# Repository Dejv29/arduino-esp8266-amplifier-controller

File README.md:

## **arduino-esp8266-amplifier-controller**  

Hybrid analog/digital amplifier controller with IR learning, motorized ALPS potentiometer feedback and ESP8266 web API.

# **Arduino + ESP8266 Amplifier Controller**  

This project is a comprehensive control system for a classic analog amplifier built using an Arduino Nano and ESP8266. The goal was to preserve the original analog character of the amplifier (including manual volume control) while adding modern features such as IR control, a web interface, a remote terrace panel, and a network API.  

The module is designed as an upgrade for a previous system based on the CD4017N microcontroller. The PCB is connected to a socket in place of the CD4017N.

### **Architecture**

The system is divided into two parts:  

#### **Arduino Nano**  

- Control of the ALPS motorized potentiometer (volume)  

- Reading the current position of the rotary volume knob via an analog input (with an added trim potentiometer for feedback)  

- IR receiver with the ability to learn up to 10 codes for each function (stored in EEPROM)  

- Control of input relays and speaker switching relays  

- RGB LED indication of the currently selected input  

#### **ESP8266**

- Web server with configuration and control interface  

- HTTP API for external control  

- Serial communication with the Arduino  

Both parts operate independently – a WiFi outage does not affect the basic functionality of the amplifier.  

### **Features**

#### **IR Learning (EEPROM)**  

Each function can have up to 10 different IR codes assigned:  

- Volume +  
- Volume -  
- Power  
- Input  
- Speakers  
- Media Play/Pause  
- Media Next  
- Media Previous  

This allows multiple remote controls to be used simultaneously.  

#### **Volume – Hybrid Solution**  

An ALPS motorized potentiometer is used.  

Analog position sensing has been added, which means:  

- the volume can be adjusted by the motor (IR, web, HW buttons)  
- it can also be changed manually by turning the knob  
- the Arduino always knows the current physical position  

This preserves full analog functionality while adding digital control.  

#### **Audio Inputs**  

- 6 inputs  
- RGB LED indicates the active input  
- Input 3 contains an internal Bluetooth module  
- Input 4 contains an external Bluetooth module located in the terrace panel  

Each input can have an individual maximum volume limit set to prevent speaker overload when different signal levels are used.  

#### **Speaker Switching**  

The **Speakers** function switches between:  

- Living room speakers  
- Terrace speakers  

#### **Terrace Control Panel**  

The external panel includes:  

- Hardware buttons for all functions  
- A rotary volume control  
- An IR receiver  

The amplifier can therefore be fully controlled even outside the main room.  

#### **Web Interface (ESP8266)**  

The ESP8266 runs a simple web server that allows:  

- Control of all amplifier functions  
- Learning and deleting IR codes  
- Setting maximum volume limits for individual inputs  
- Displaying the current device status  

#### **HTTP API**  

The server accepts commands in the following format:  

SET_POWER_ON / SET_POWER_OFF  

SET_VOLUME_25  

SET_INPUT_2  

SET_SPEAKER_A / SET_SPEAKER_B  

PULSE_VOLUP  

PULSE_VOLDOWN  

SET_AUTO_OFF_<value_in_seconds> / SET_AUTO_OFF_0 – cancels the timer  

IR_LEARN_POWER (VOLUP, VOLDOWN, INPUT, SPEAKERS, PLAY, NEXT, PREV)  

IR_REMOVE_POWER (VOLUP, VOLDOWN, INPUT, SPEAKERS, PLAY, NEXT, PREV )  

IR_REMOVE_POWER_ALL  

SET_MAX_VOL_INPUT__<volume_value>   (sets the specified volume value as the limit)

SET_CURRENT_MAX_VOLUME  (sets the current volume as the limit)

WIPE_EEPROM (clears the EEPROM memory)

Each request returns a response containing the complete current device status.  

This API can be easily integrated into other systems – for example into the **Tasker** app, where a simple control application using HTTP commands has been created.  

____________________________________________________________________________________________________________________________________________________________________________________________________________________________________________________________________________________________________________________________________________

# **Arduino + ESP8266 Amplifier Controller**  

Tento projekt je komplexní řídicí systém pro klasický analogový zesilovač postavený na Arduino Nano a  ESP8266. Cílem bylo zachovat původní analogový charakter zesilovače (včetně manuálního ovládání hlasitosti), ale doplnit jej o moderní funkce – IR ovládání, webové rozhraní, vzdálený panel na terase a síťové API. 

Modul je koncipován jako upgrade pro předchozí systém postavený na mikrokontroléru CD4017N. PCB je připojena do patice na místo CD4017N.

### **Architektura**

Systém je rozdělen na dvě části:  

#### **Arduino Nano**  

- Řízení motorizovaného potenciometru ALPS (hlasitost)  

- Snímání aktuální polohy otočného ovladače hlasitosti přes analogový vstup (přidaný trimr pro zpětnou vazbu)  

- IR přijímač s možností učení až 10 kódů na každou funkci (uloženo v EEPROM)  

- Ovládání relé vstupů a reproduktorových větví  

- RGB LED indikace aktuálního vstupu  

#### **ESP8266**

- Web server s konfiguračním a ovládacím rozhraním  

- HTTP API pro externí řízení  

- Sériová komunikace s Arduinem 

 Obě části fungují nezávisle – výpadek WiFi neovlivní základní funkčnost zesilovače.  

### **Funkce**

#### **IR učení (EEPROM)**  

Každé funkci lze přiřadit až 10 různých IR kódů:  

- Volume +  
- Volume -  
- Power  
- Input  
- Speakers  
- Media Play/Pause  
- Media Next  
- Media Previous  

To umožňuje používat více dálkových ovladačů současně.  

#### **Hlasitost – hybridní řešení**  

Použit je motorizovaný potenciometr ALPS.  

   Bylo doplněno analogové snímání polohy, takže:  
- hlasitost lze měnit motorem (IR, web, HW tlačítka)  
- lze ji měnit i ručně otočením knobu  
- Arduino vždy zná aktuální fyzickou polohu

 Zachována je tedy plná analogová funkčnost, ale s digitální kontrolou.  

#### **Audio vstupy**  

- 6 vstupů  
- RGB LED indikuje aktivní vstup  
- Na vstupu 3 je interní Bluetooth modul  
- Na vstupu 4 je externí Bluetooth modul umístěný v terasovém panelu  

 Pro každý vstup lze nastavit individuální maximální limit hlasitosti, aby nedošlo k přetížení reproduktorů při různých úrovních signálu.  

#### **Přepínání reproduktorů**  

Funkce **Speakers** přepíná mezi:  

- Reproduktory v obýváku  
- Reproduktory na terase  

#### **Terasový ovládací panel**  

Externí panel obsahuje:  

- HW tlačítka pro všechny funkce  
- Otočný ovladač hlasitosti  
- IR přijímač  

 Zesilovač je tedy plně ovladatelný i mimo hlavní místnost.  

#### **Webové rozhraní (ESP8266)**  

ESP8266 provozuje jednoduchý web server, který umožňuje:  

- Ovládání všech funkcí zesilovače  
- Učení a mazání IR kódů  
- Nastavení maximální hlasitosti pro jednotlivé vstupy  
- Zobrazení aktuálního stavu zařízení  

#### **HTTP API**  

Server přijímá příkazy ve formátu:  

SET_POWER_ON / SET_POWER_OFF  

SET_VOLUME_25  

SET_INPUT_2  

SET_SPEAKER_A / SET_SPEAKER_B

PULSE_VOLUP  

PULSE_VOLDOWN  

SET_AUTO_OFF_<hodnota_v_sekundách> / SET_AUTO_OFF_0 – zruší časovač 

IR_LEARN_POWER (VOLUP, VOLDOWN, INPUT, SPEAKERS, PLAY, NEXT, PREV)  

IR_REMOVE_POWER (VOLUP, VOLDOWN, INPUT, SPEAKERS, PLAY, NEXT, PREV )  

IR_REMOVE_POWER_ALL  

SET_MAX_VOL_INPUT__<hodnota_volume>   (nastaví zadanou hodnotu hlasitosti jako limit)

SET_CURRENT_MAX_VOLUME  (nastaví současnou hlasitost jako limit)

WIPE_EEPROM (vymaže paměť EEPROM)

​    

 Každý požadavek vrací odpověď obsahující kompletní aktuální stav zařízení.  

 Toto API lze snadno integrovat do jiných systémů – například do aplikace **Tasker**, kde je vytvořena jednoduchá ovládací aplikace využívající HTTP příkazy  

​

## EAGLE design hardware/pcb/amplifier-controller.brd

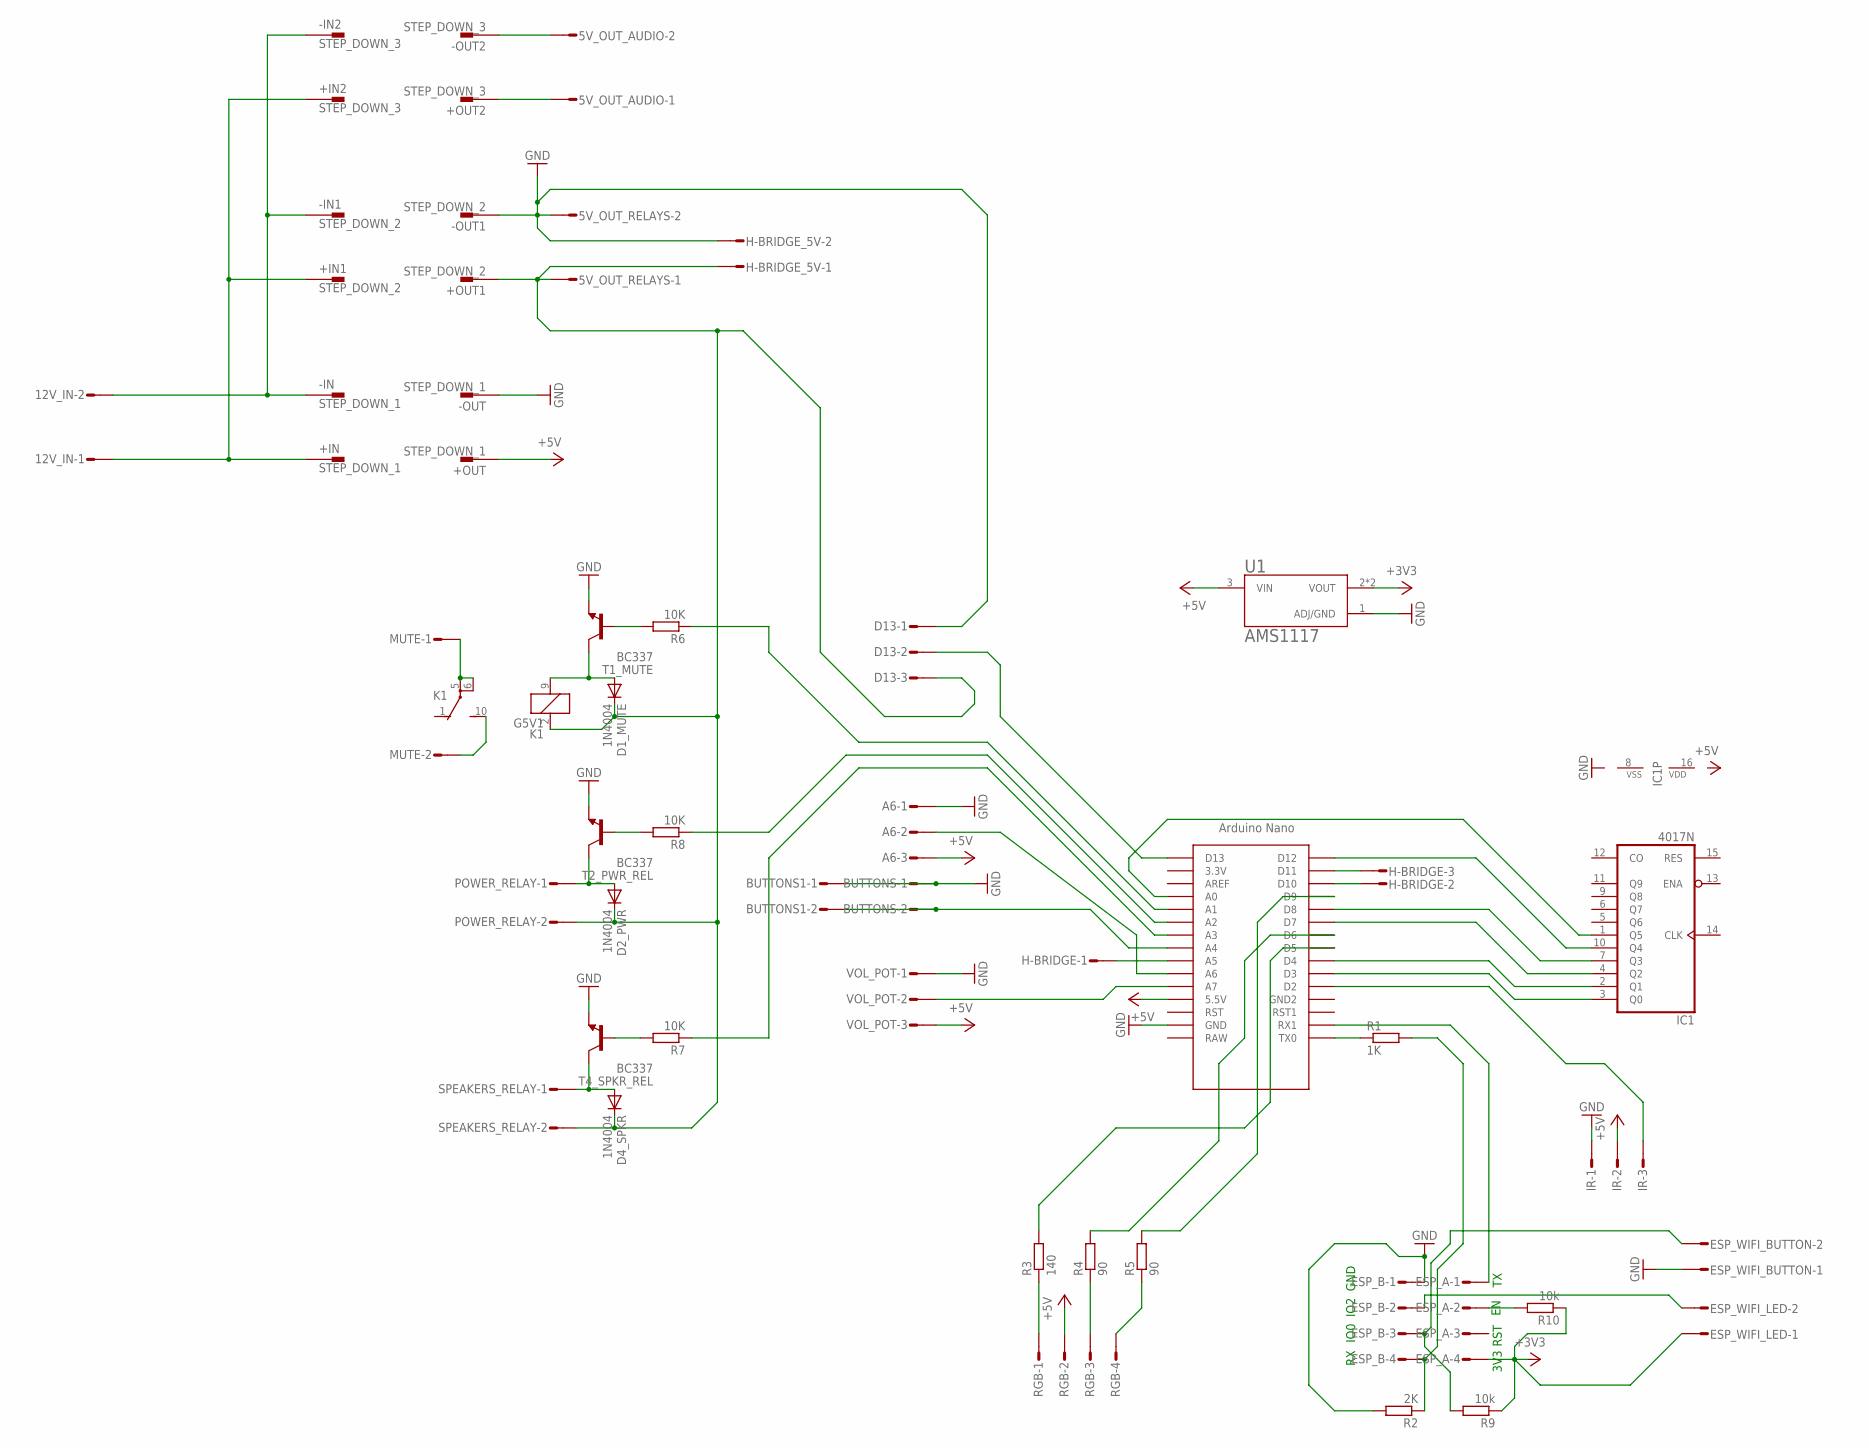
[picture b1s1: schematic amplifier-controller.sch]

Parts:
5V_OUT_AUDIO, 5V_OUT_RELAYS, 12V_IN: L02P
+IN: STEP_DOWN_1; 62221
+IN1: STEP_DOWN_2; 62221
+IN2: STEP_DOWN_3; 62221
+OUT: STEP_DOWN_1; 62221
+OUT1: STEP_DOWN_2; 62221
+OUT2: STEP_DOWN_3; 62221
-IN: STEP_DOWN_1; 62221
-IN1: STEP_DOWN_2; 62221
-IN2: STEP_DOWN_3; 62221
-OUT: STEP_DOWN_1; 62221
-OUT1: STEP_DOWN_2; 62221
-OUT2: STEP_DOWN_3; 62221
A6: L03P
BUTTONS, BUTTONS1: L02P
D1_MUTE, D2_PWR, D4_SPKR: 1N4004; DO41-10
D13: L03P
ESP_A: L04P
ESP_B: L04P
ESP_WIFI_BUTTON: L02P
ESP_WIFI_LED: L02P
H-BRIDGE: L03P
H-BRIDGE_5V: L02P
IC1: 4017N; DIL16
IR: L03P
K1: G5V1
MUTE: L02P
POWER_RELAY: L02P
R1: 1K; 0411/15
R2: 2K; 0411/15
R3: 140; 0411/15
R4, R5: 90; 0411/15
R6, R8: 10K; 0309/12
R7: 10K; 0617/22
R9, R10: 10k; 0411/15
RGB: L04P
SPEAKERS_RELAY: L02P
T1_MUTE, T2_PWR_REL, T4_SPKR_REL: BC337; TO92
U1: AMS1117; SOT229P700X180-4N
U$1: NANO
VOL_POT: L03P

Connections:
+3V3: ESP_A.4, ESP_WIFI_LED.1, R9.1, R10.1, U1.2 (VOUT), U1.4 (VOUT)
+5V: +OUT.1, A6.3, IR.2, RGB.2, U1.3 (VIN), U$1.5V (5.5V), VOL_POT.3
GND: 5V_OUT_RELAYS.2, -OUT.1, -OUT1.1, A6.1, BUTTONS.1, BUTTONS1.1, D13.1, ESP_B.1, ESP_WIFI_BUTTON.1, H-BRIDGE_5V.2, IR.1, R2.2, T1_MUTE.1 (E), T2_PWR_REL.1 (E), T4_SPKR_REL.1 (E), U1.1 (ADJ/GND), U$1.GND, VOL_POT.1
unnamed: ESP_B.4, R1.2, R2.1
unnamed: R1.1, U$1.TX0
unnamed: IR.3, U$1.D2
unnamed: IC1.3 (Q0), U$1.D3
unnamed: IC1.2 (Q1), U$1.D4
unnamed: IC1.4 (Q2), U$1.D7
unnamed: IC1.7 (Q3), U$1.D8
unnamed: IC1.10 (Q4), U$1.D12
unnamed: IC1.1 (Q5), U$1.A0
unnamed: H-BRIDGE.1, U$1.A5
unnamed: H-BRIDGE.2, U$1.D10
unnamed: H-BRIDGE.3, U$1.D11
unnamed: U$1.A7, VOL_POT.2
unnamed: BUTTONS.2, BUTTONS1.2, U$1.A4
unnamed: R3.1, RGB.1
unnamed: R4.1, RGB.3
unnamed: R5.1, RGB.4
unnamed: R3.2, U$1.D5
unnamed: R4.2, U$1.D6
unnamed: R5.2, U$1.D9
unnamed: D13.2, U$1.D13
unnamed: A6.2, U$1.A6
unnamed: ESP_B.3, ESP_WIFI_BUTTON.2, R9.2
unnamed: ESP_A.1, U$1.RX1
unnamed: D4_SPKR.A, SPEAKERS_RELAY.1, T4_SPKR_REL.3 (C)
unnamed: R7.2, T4_SPKR_REL.2 (B)
unnamed: R6.2, T1_MUTE.2 (B)
unnamed: R6.1, U$1.A1
unnamed: R7.1, U$1.A3
unnamed: D1_MUTE.A, K1.9 (2), T1_MUTE.3 (C)
unnamed: R8.2, T2_PWR_REL.2 (B)
unnamed: R8.1, U$1.A2
unnamed: D2_PWR.A, POWER_RELAY.1, T2_PWR_REL.3 (C)
unnamed: ESP_A.2, R10.2
unnamed: 12V_IN.2, -IN.1, -IN1.1, -IN2.1
unnamed: ESP_B.2, ESP_WIFI_LED.2
unnamed: 12V_IN.1, +IN.1, +IN1.1, +IN2.1
unnamed: K1.5, K1.6, MUTE.1
unnamed: K1.10 (S), MUTE.2
unnamed: 5V_OUT_AUDIO.1, +OUT2.1
unnamed: 5V_OUT_AUDIO.2, -OUT2.1
unnamed: 5V_OUT_RELAYS.1, +OUT1.1, D1_MUTE.C, D2_PWR.C, D4_SPKR.C, D13.3, H-BRIDGE_5V.1, K1.2 (1), POWER_RELAY.2, SPEAKERS_RELAY.2
VDD: IC1.16 (VDD)
VSS: IC1.8 (VSS)

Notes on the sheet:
3V3
RST
IO0
IO2
GND

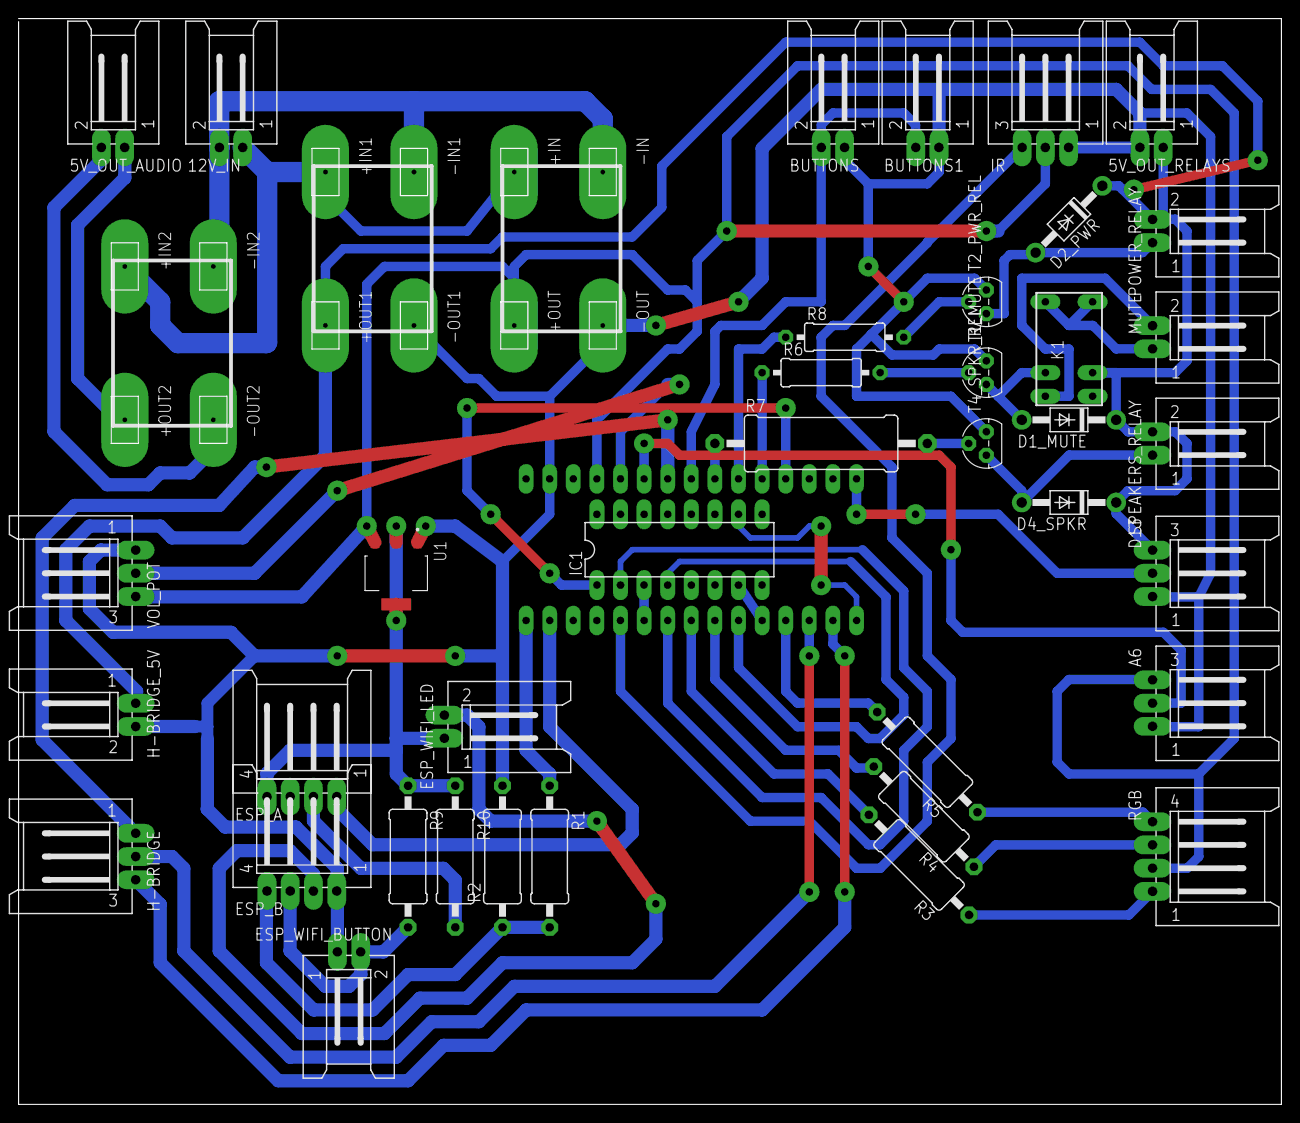
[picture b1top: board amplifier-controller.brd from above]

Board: 2 copper layers, 135.9 x 116.8 mm, 51 parts (0 on the bottom side), 45 nets.

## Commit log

2026-03-12 Initial commit: Arduino amplifier controller
2026-03-12 Remove duplicate readme.md
2026-03-12 Update README documentation
2026-03-12 Update LICENSE
2026-03-13 Update README, added images, added PCB and schematics
2026-03-13 Update README, added english readme
2026-03-16 Rename Zesilovac_DC_Motor_MEDIA_BTN_ino.ino to Nano_Amp.ino
2026-03-16 Rename Zesilovac_WIFI_AP.ino to ESP8266_Wifi_AP.ino
2026-03-16 Removed unnecessary comments
2026-03-16 Added PDF scheamtic
2026-03-18 Added WebUI images
2026-03-18 Added Tasker UI image
